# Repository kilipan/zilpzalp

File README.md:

# zilpzalp
A wonky 28-key, column-staggered, unibody-split keyboard made with fantastic FOSS software: [ergogen](https://github.com/ergogen/ergogen) and [KiCad](https://www.kicad.org/).

For buying ready-to-assemble kits, consider [keeb.supply](https://keeb.supply/products/zilpzalp)! They share part of the profits made by selling zilpzalp with me!

Four versions for choc switches are available:
- the choc version with support for optional hotswap sockets and slightly extended edgecuts to acommodate the extra space required by the socket (in the [pcb](https://github.com/kilipan/zilpzalp/tree/main/pcb) directory)
- the cfx version with different spacing, making the zilpzalp almost 1.5 cm smaller horizontally (in the [pcb_cfx_spacing](https://github.com/kilipan/zilpzalp/tree/main/pcb_cfx_spacing) directory)
- the default-spacing solder-only version with tighter edge cuts (in the [pcb_solder_only](https://github.com/kilipan/zilpzalp/tree/main/pcb_solder_only) directory)
- the minimal-choc-spacing solder-only version with the tightest spacing that choc V1 switches allow for (in the [pcb_minimal_choc](https://github.com/kilipan/zilpzalp/tree/main/pcb_minimal_choc) directory)  
  **Note:** You will have to procure minimal-spacing keycaps. I am not aware of any commercial solution. Recommendation: [Philadelphia Minimalist](https://github.com/pseudoku/PseudoMakeMeKeyCapProfiles/blob/master/Philadelphia_Minimalist.scad) by [Pseudoku](https://github.com/pseudoku)

One version for MX, KS-27, and KS-33 switches is available:
- this version has default MX-spacing and features a hybrid switch-footprint for hotswap-only MX and solder-only KS-27/33 (in the [pcb_mx_spacing](https://github.com/kilipan/zilpzalp/tree/main/pcb_mx_spacing) directory)

**Warning:** The solder-only default choc-spacing version has not been tested yet!

Some example keymaps for getting an idea of how zilpzalp may be used can be found in the [`example_keymaps` directory](https://github.com/kilipan/zilpzalp/tree/main/example_keymaps).

## BOM
- 1 pcb
- 1 Seeed XIAO compatible controller, like e.g. [Miao](https://github.com/kilipan/miao)
- 14 sot23 diodes (common cathode)
- optional (for hot swap versions only): 28 hot swap sockets  
  (choc or mx depending on pcb version)
- 28 kailh choc low profile switches
- 28 fitting keycaps (pay special attention here when building the cfx or minimal-spacing version!)

## Firmware
I personally use and recommend [ZMK firmware](https://github.com/kilipan/zmk-config-zilpzalp) which is tested and confirmed-functional for the Seeed XIAO RP2040 and the Seeed XIAO BLE controllers.  
Check out [FAK firmware](https://github.com/semickolon/fak) if you're planning to use the Miao!  
[QMK firmware](https://github.com/kilipan/qmk-config-zilpzalp) for the Seeed XIAO RP2040 is also available.

## Inspiration
- all the fantastic keyboards, knowledge, and help by [GEIST](https://github.com/GEIGEIGEIST/), [Freya](https://linktr.ee/freya_irl), [Bob](https://github.com/GroooveBob), and the wonderful Clacktales keyboard community
- the [hummingbird](https://github.com/PJE66/hummingbird) keyboard and the [rufous](https://github.com/jcmkk3/trochilidae#rufous) variation
- the [aptmak](https://github.com/apsu/aptmak) keymap

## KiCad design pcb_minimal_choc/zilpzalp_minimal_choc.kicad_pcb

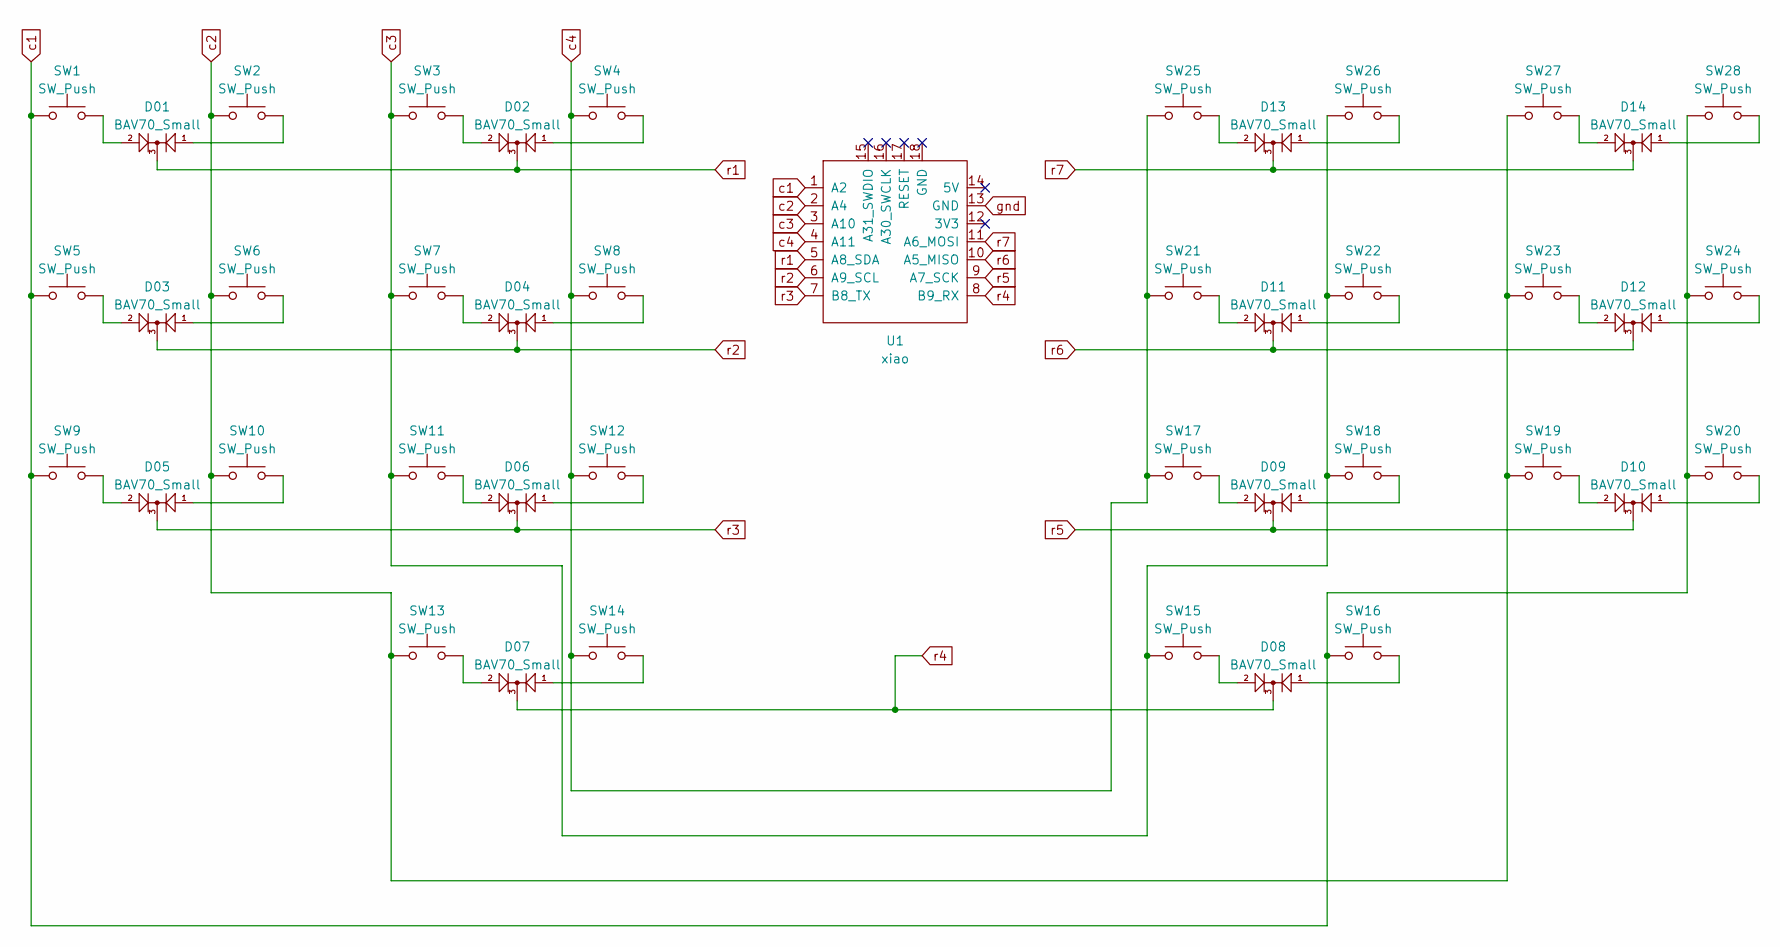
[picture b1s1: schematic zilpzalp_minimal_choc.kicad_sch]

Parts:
D01, D02, D03, D04, D05, D06, D07, D08, D09, D10, D11, D12, D13, D14: BAV70_Small; SOT-23_Handsoldering
SW1, SW2, SW3, SW4, SW5, SW6, SW7, SW8, SW9, SW10, SW11, SW12, SW13, SW14, SW15, SW16, SW17, SW18, SW19, SW20, SW21, SW22, SW23, SW24, SW25, SW26, SW27, SW28: SW_Push; SW_Kailh-PG1350-1u-NoLED
U1: xiao; xiao-tht

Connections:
unnamed: D01.1 (A1), SW2.2
unnamed: D01.2 (A2), SW1.2
unnamed: D02.1 (A1), SW4.2
unnamed: D02.2 (A2), SW3.2
unnamed: D03.1 (A1), SW6.2
unnamed: D03.2 (A2), SW5.2
unnamed: D04.1 (A1), SW8.2
unnamed: D04.2 (A2), SW7.2
unnamed: D05.1 (A1), SW10.2
unnamed: D05.2 (A2), SW9.2
unnamed: D06.1 (A1), SW12.2
unnamed: D06.2 (A2), SW11.2
unnamed: D07.1 (A1), SW14.2
unnamed: D07.2 (A2), SW13.2
unnamed: D08.1 (A1), SW16.2
unnamed: D08.2 (A2), SW15.2
unnamed: D09.1 (A1), SW18.2
unnamed: D09.2 (A2), SW17.2
unnamed: D10.1 (A1), SW20.2
unnamed: D10.2 (A2), SW19.2
unnamed: D11.1 (A1), SW22.2
unnamed: D11.2 (A2), SW21.2
unnamed: D12.1 (A1), SW24.2
unnamed: D12.2 (A2), SW23.2
unnamed: D13.1 (A1), SW26.2
unnamed: D13.2 (A2), SW25.2
unnamed: D14.1 (A1), SW28.2
unnamed: D14.2 (A2), SW27.2
c1: SW1.1, SW5.1, SW9.1, SW16.1, SW20.1, SW24.1, SW28.1, U1.1 (A2)
c2: SW2.1, SW6.1, SW10.1, SW13.1, SW19.1, SW23.1, SW27.1, U1.2 (A4)
c3: SW3.1, SW7.1, SW11.1, SW15.1, SW18.1, SW22.1, SW26.1, U1.3 (A10)
c4: SW4.1, SW8.1, SW12.1, SW14.1, SW17.1, SW21.1, SW25.1, U1.4 (A11)
gnd: U1.13 (GND)
r1: D01.3 (K), D02.3 (K), U1.5 (A8_SDA)
r2: D03.3 (K), D04.3 (K), U1.6 (A9_SCL)
r3: D05.3 (K), D06.3 (K), U1.7 (B8_TX)
r4: D07.3 (K), D08.3 (K), U1.8 (B9_RX)
r5: D09.3 (K), D10.3 (K), U1.9 (A7_SCK)
r6: D11.3 (K), D12.3 (K), U1.10 (A5_MISO)
r7: D13.3 (K), D14.3 (K), U1.11 (A6_MOSI)

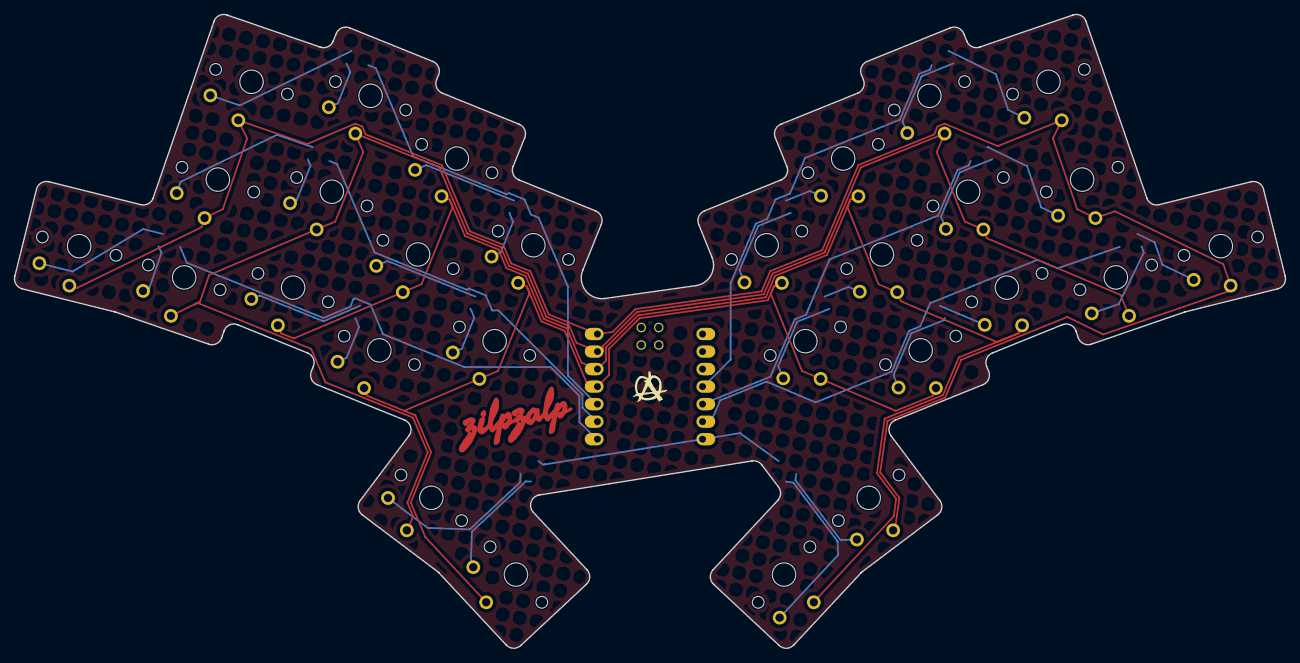
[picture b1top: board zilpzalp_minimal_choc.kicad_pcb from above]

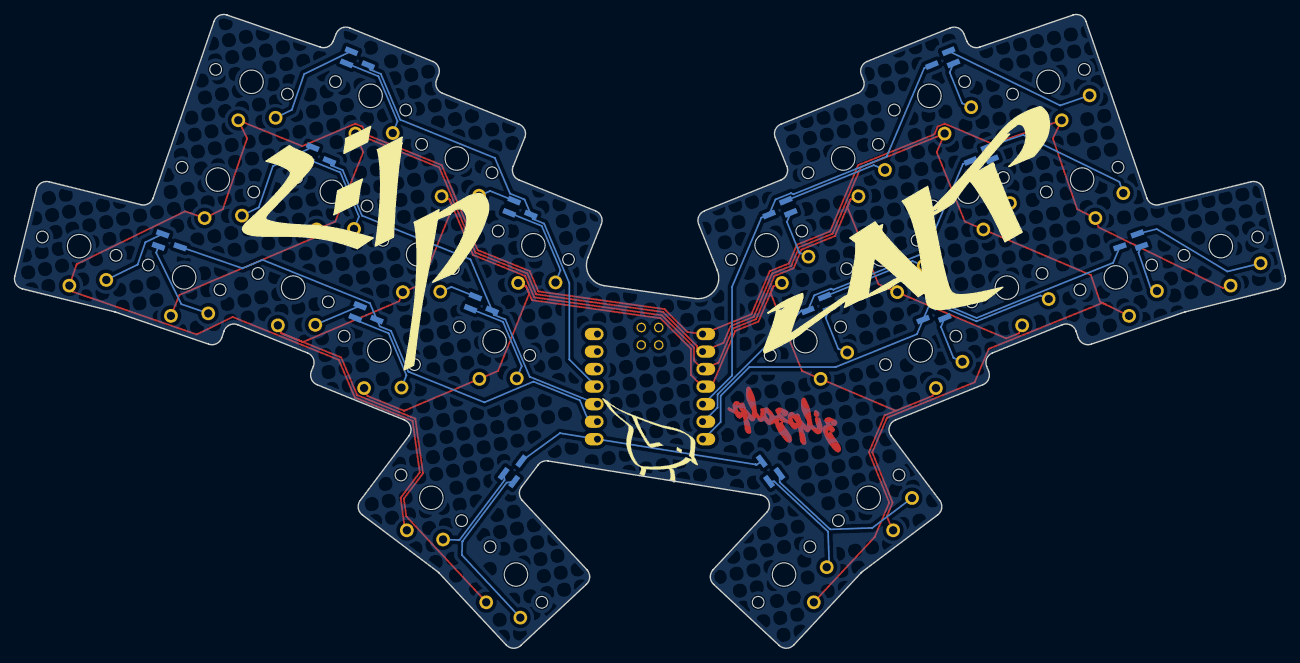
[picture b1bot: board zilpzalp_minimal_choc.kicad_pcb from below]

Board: 2 copper layers, 184.3 x 91.9 mm, 43 parts (14 on the bottom side), 39 nets.

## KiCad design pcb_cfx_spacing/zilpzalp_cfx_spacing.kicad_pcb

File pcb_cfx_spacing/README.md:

# CFX VERSION
**Warning:** This pcb version uses tighter spacing between switches and **most common keycaps do not fit!**  
  
This pcb was designed for Chosfox's Chocfox (a.k.a. CFX) keycaps' spacing in mind. That means only **square** keycaps with 16.5 mm by 16.5 mm (or smaller) will fit.

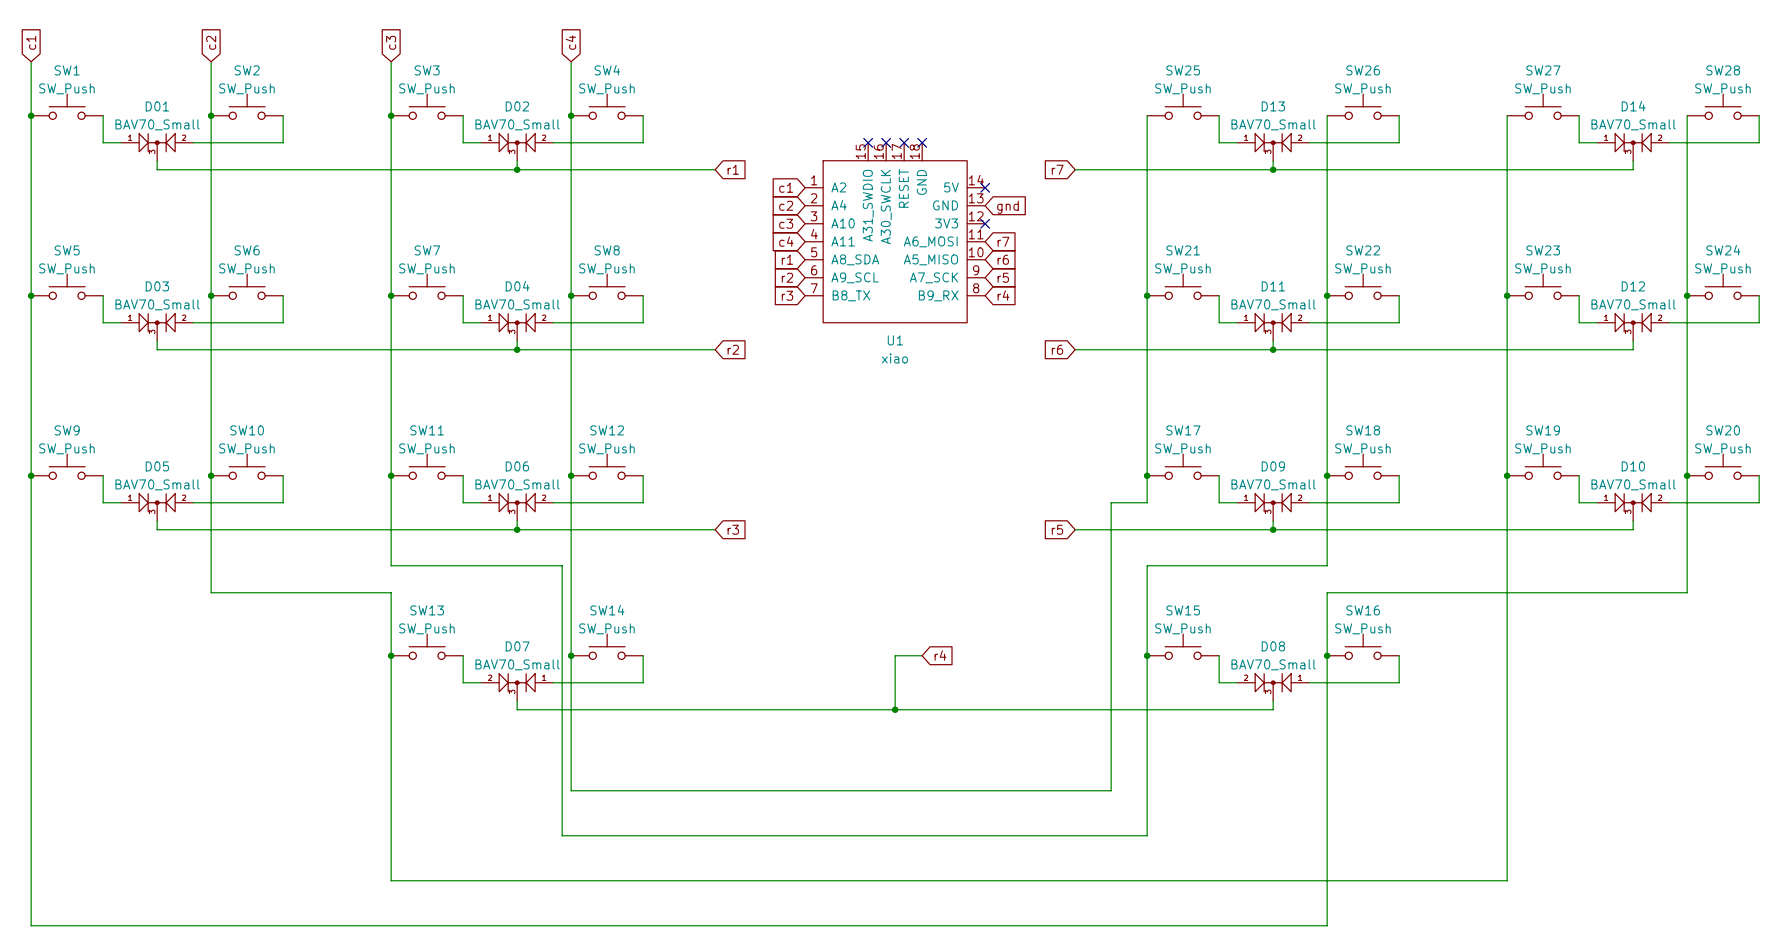
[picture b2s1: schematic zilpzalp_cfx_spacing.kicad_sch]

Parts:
D01, D02, D03, D04, D05, D06, D07, D08, D09, D10, D11, D12, D13, D14: BAV70_Small; SOT-23_Handsoldering
SW1, SW2, SW3, SW4, SW5, SW6, SW7, SW8, SW9, SW10, SW11, SW12, SW13, SW14, SW15, SW16, SW17, SW18, SW19, SW20, SW21, SW22, SW23, SW24, SW25, SW26, SW27, SW28: SW_Push; SW_Kailh_choc_hs_plus_solder_no_silk
U1: xiao; xiao-tht

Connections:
unnamed: D01.1 (A1), SW1.2
unnamed: D01.2 (A2), SW2.2
unnamed: D02.1 (A1), SW3.2
unnamed: D02.2 (A2), SW4.2
unnamed: D03.1 (A1), SW5.2
unnamed: D03.2 (A2), SW6.2
unnamed: D04.1 (A1), SW7.2
unnamed: D04.2 (A2), SW8.2
unnamed: D05.1 (A1), SW9.2
unnamed: D05.2 (A2), SW10.2
unnamed: D06.1 (A1), SW11.2
unnamed: D06.2 (A2), SW12.2
unnamed: D07.1 (A1), SW14.2
unnamed: D07.2 (A2), SW13.2
unnamed: D08.1 (A1), SW16.2
unnamed: D08.2 (A2), SW15.2
unnamed: D09.1 (A1), SW17.2
unnamed: D09.2 (A2), SW18.2
unnamed: D10.1 (A1), SW19.2
unnamed: D10.2 (A2), SW20.2
unnamed: D11.1 (A1), SW21.2
unnamed: D11.2 (A2), SW22.2
unnamed: D12.1 (A1), SW23.2
unnamed: D12.2 (A2), SW24.2
unnamed: D13.1 (A1), SW25.2
unnamed: D13.2 (A2), SW26.2
unnamed: D14.1 (A1), SW27.2
unnamed: D14.2 (A2), SW28.2
c1: SW1.1, SW5.1, SW9.1, SW16.1, SW20.1, SW24.1, SW28.1, U1.1 (A2)
c2: SW2.1, SW6.1, SW10.1, SW13.1, SW19.1, SW23.1, SW27.1, U1.2 (A4)
c3: SW3.1, SW7.1, SW11.1, SW15.1, SW18.1, SW22.1, SW26.1, U1.3 (A10)
c4: SW4.1, SW8.1, SW12.1, SW14.1, SW17.1, SW21.1, SW25.1, U1.4 (A11)
gnd: U1.13 (GND)
r1: D01.3 (K), D02.3 (K), U1.5 (A8_SDA)
r2: D03.3 (K), D04.3 (K), U1.6 (A9_SCL)
r3: D05.3 (K), D06.3 (K), U1.7 (B8_TX)
r4: D07.3 (K), D08.3 (K), U1.8 (B9_RX)
r5: D09.3 (K), D10.3 (K), U1.9 (A7_SCK)
r6: D11.3 (K), D12.3 (K), U1.10 (A5_MISO)
r7: D13.3 (K), D14.3 (K), U1.11 (A6_MOSI)

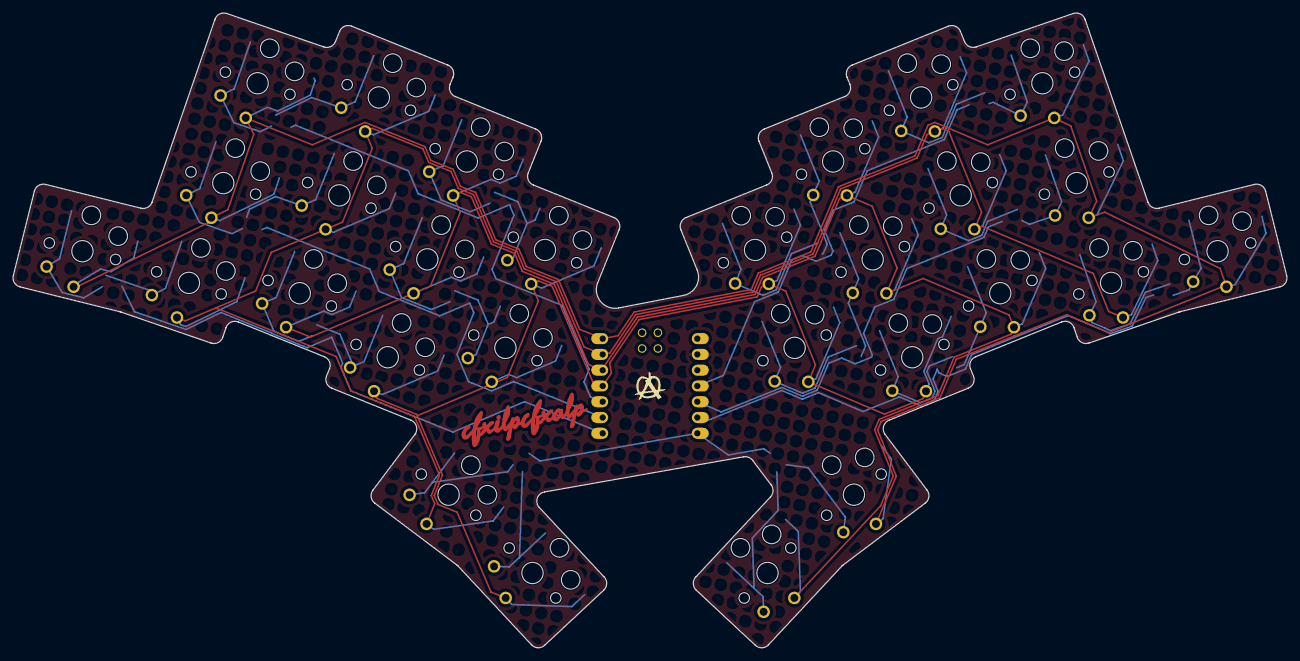
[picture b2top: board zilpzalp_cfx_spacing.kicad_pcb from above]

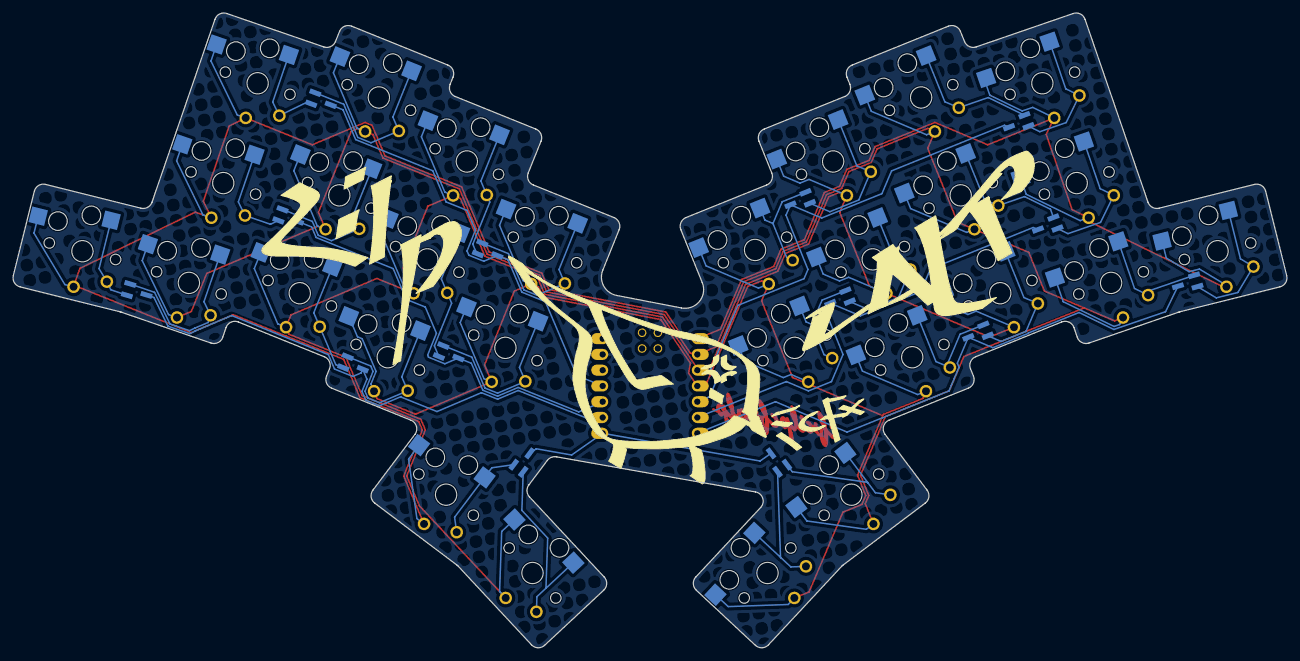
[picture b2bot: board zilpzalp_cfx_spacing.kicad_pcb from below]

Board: 2 copper layers, 205.1 x 102.2 mm, 43 parts (14 on the bottom side), 39 nets.

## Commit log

2023-03-09 add pcb files
2023-03-09 add license
2023-03-10 add ground fill and silk
2023-03-10 change xiao footprint, silk slightly smaller
2023-03-10 update readme, make all pcb layers visible by default
2023-03-10 add gerbers
2023-03-12 add solder-only version
2023-03-29 add photo of the finished build and update README
2023-04-01 add cfx spacing version
2023-04-01 add warning to cfx spacing pcb directory
2023-04-01 fix readme
2023-04-02 beautify routing slightly
2023-04-28 add minimal-spacing version
2023-05-17 add example keymaps
2023-05-17 add example keymap directory
2023-05-17 add license for keymap examples
2023-05-17 add note about example keymaps
2023-05-17 add link to ZMK firmware
2023-05-17 fix typos
2023-05-17 mention keeb.supply shop page
2023-05-28 add mx/ks version
2023-05-29 add mounting holes
2023-05-29 add top & bottom plate files
2023-06-13 remove untested warning for minizilp/mx-ks-version
2023-10-18 mention verified xiao ble zmk firmware
2023-12-13 fix copyright notice
